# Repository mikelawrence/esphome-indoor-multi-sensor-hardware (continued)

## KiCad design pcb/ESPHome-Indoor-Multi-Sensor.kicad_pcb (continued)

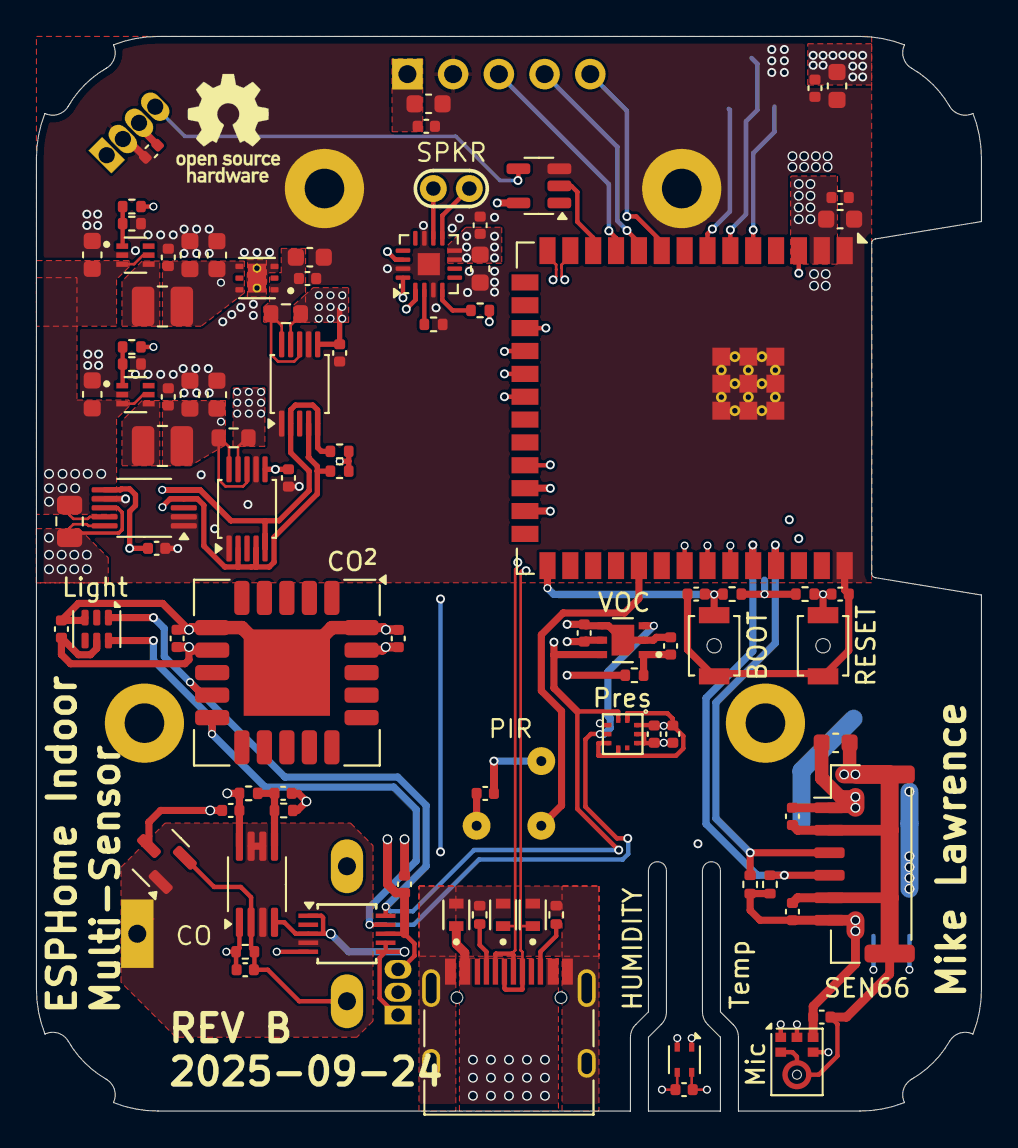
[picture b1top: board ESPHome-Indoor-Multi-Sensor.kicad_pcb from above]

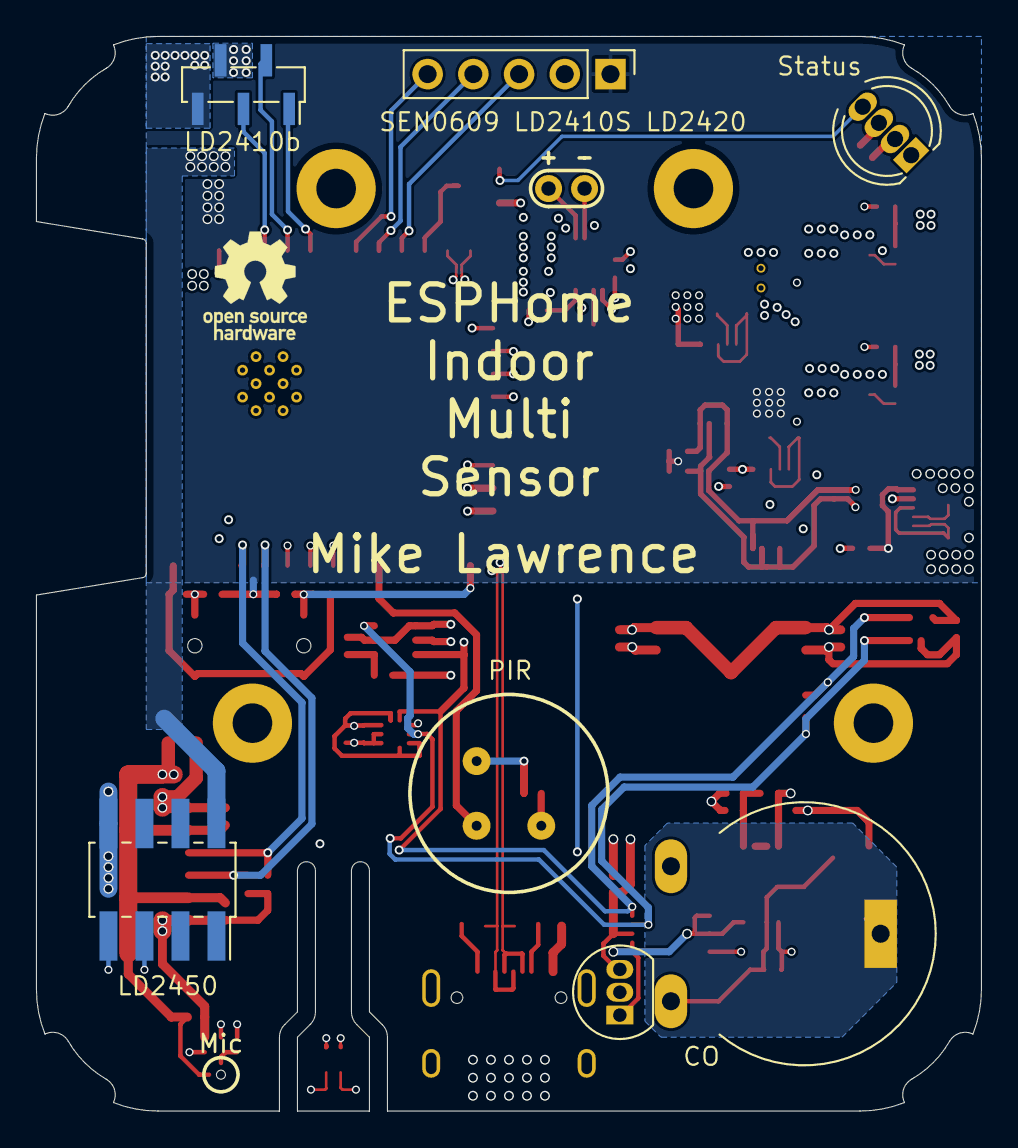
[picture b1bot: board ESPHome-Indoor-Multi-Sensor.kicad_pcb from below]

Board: 4 copper layers, 52.5 x 59.7 mm, 113 parts (9 on the bottom side), 48 nets.

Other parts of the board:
T1, T2, T3, T4, T5, T6, T7, T8, T9, T10: Tab
TEXT0, TEXT0#2: OSHW-Logo_5.7x6mm_SilkScreen

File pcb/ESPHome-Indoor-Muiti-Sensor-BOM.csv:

"Qty","Reference","Value","Description","DNP","Manufacturer","Part Number"
"11","C1,C4,C5,C22,C25,C26,C27,C31,C34,C36,C37","1uF","Capacitor, 1uF, MLCC, 25V, X5R, 10%, 0402","","Samsung","CL05A105KA5NQNC"
"12","C2,C3,C8,C9,C11,C12,C13,C15,C16,C18,C19,C30","22uF","Capacitor, 22uF, MLCC, 6.3V, X5R, 20%, 0603","","Murata","GRM188R60J226MEA0D"
"18","C6,C7,C10,C14,C17,C20,C21,C23,C24,C28,C29,C32,C33,C35,C38,C39,C40,C41","100nF","Capacitor, 100nF, MLCC, 50V, X7R, 10%, 0402","","Samsung","CL05B104KB54PNC"
"1","D4","NeoPixel_THT","RGB LED with integrated controller, 5mm/8mm LED package","","Adafruit","1938"
"3","D1,D2,D3","ESDA8P80-1U1M","TVS, Unidirectional high power, QFN-2","","STMicroelectronics","ESDA8P80-1U1M"
"1","J1","SEN66","6-Position, 1.25 mm pitch, Wire-to-Board connector","","JST","BM06B-GHS-TBT"
"1","J2","USB-C","Connector, USB 2.0, 16P, Type-C, Receptacle","","Phoenix Contact","1332645"
"1","J3","SEN0609","Generic connector, 2.54mm spacing, single row, 01x05 (TLW-105-06-T-S)","","Samtec","CES-105-01-T-S"
"1","J4","LD2410","Generic connector, 1.27mm spacing, single row, 01x05","","Samtec","RSM-105-02-S-S"
"1","J5","SPKR","Solder Holes for up to 24 ga wire","","Same Sky","CMS-251437-24SP-X8 "
"1","J6","LD2450","Socket, 8 position, 2mm spacing, dual row, 02x04, SMT","","Molex","79109-1003"
"2","L1,L2","1uH","Inductor, 1uH, 3.3A, 20%, 1008","","Murata","DFE252012F-1R0M=P2"
"1","MK1","ICS-43434","TDK InvenSense MEMS Microphone, 24-bit I2S, 65 dBA SNR, LGA-6","","TDK InvenSense","ICS-43434"
"1","Q1","MMBFJ201","20mA min, 35V, 30mOhm max, 3-10V Vgs(off), N-Channel JFET, SOT-23","","Onsemi","MMBFJ201"
"1","R1","499KΩ","Resistor, 499KΩ, 62.5mW, 1%, 0402","","Vishay / Dale","CRCW0402499KFKED"
"1","R3","634KΩ","Resistor, 634KΩ, 62.5mW, 1%, 0402","","Vishay / Dale","CRCW0402634KFKED"
"1","R4","453KΩ","Resistor, 453KΩ, 62.5mW, 1%, 0402","","Vishay / Dale","CRCW0402453KFKED"
"1","R8","68mΩ","Current Sense Resistor, 68mΩ, 400mW, 1%, 75ppm, 0603","","Vishay","WSLP0603R0680FEA"
"1","R9","150mΩ","Current Sense Resistor, 150mΩ, 250mW, 1%, 75ppm, 0805","","Vishay","WSL0805R1500FEA18"
"1","R10","80mΩ","Current Sense Resistor, 80mΩ, 400mW, 1%, 75ppm, 0603","","Vishay","WSLP0603R0800FEB"
"1","R14","4.7Ω","Resistor, 4.7Ω, 62.5mW, 1%, 0402","","Vishay / Dale","CRCW04024R70FKED"
"1","R15","64.9KΩ","Resistor, 64.9KΩ, 62.5mW, 1%, 0402","","Vishay / Dale","CRCW040264K9FKED "
"1","R21","133KΩ","Resistor, 133KΩ, 62.5mW, 1%, 0402","","Vishay / Dale","CRCW0402133KFKED"
"2","R12,R13","10KΩ","Resistor, 10KΩ, 62.5mW, 1%, 0402","","Vishay / Dale","CRCW040210K0FKED"
"4","R2,R5,R11,R16","100KΩ","Resistor, 100KΩ, 62.5mW, 1%, 0402","","Vishay / Dale","CRCW0402100KFKED"
"6","R6,R7,R17,R18,R19,R20","5.1KΩ","Resistor, 5.1KΩ, 62.5mW, 1%, 0402","DNP","Vishay / Dale","CRCW04025K10FKED"
"1","SW1","BOOT","Switch, SMD","","Omron","B3U-1000P"
"1","SW2","RESET","Switch, SMD","","Omron","B3U-1000P"
"1","U1","SN74LV1T34DBV","IC, Single Power Supply, Single Buffer GATE, CMOS Logic, Level Shifter, SOT-23-5","","Texas Instruments","SN74LV1T34DBV"
"1","U3","MAX98357A","Mono DAC with amplifier, I2S, PCM, TDM, 32-bit, 96khz, 3.2W, TQFP-16","","Maxim","MAX98357AETE"
"1","U4","TLV75533PDRV","500mA Low Dropout Voltage Regulator, Fixed Output 3.3V, WSON6","","Texas Instruments","TLV75533PDRV"
"1","U6","ESP32-S3-WROOM-2-N32R16V","RF Module, ESP32-S3 SoC, Wi-Fi 802.11b/g/n, Bluetooth, BLE, 32-bit, 3.3V, onboard antenna, SMD","","Espressif","ESP32-S3-WROOM-2-N32R16V"
"1","U7","INA228","IC, 85-V, 20-Bit, Ultra-Precise Power-Energy-Charge Monitor With I2C Interface, VSSOP-10","","Texas Instruments","INA228AIDGSR"
"1","U8","TSL2591","Light to digital converter, 2.7 to 3.6V Vdd, DFN-6","","AMS","TSL2591"
"1","U9","SGP41","Indoor Air Quality Sensor, MOx based, DFN-6","","Sensirion","SGP41-D-R4 "
"1","U10","SCD41","Photoacoustic CO2 sensor, I2C, 2.4-5.5 V, High accuracy  400 - 5000 ppm","","Sensirion","SCD41-D-R2"
"1","U11","BMP581","Barometric Pressure Sensor, 24-bit, Low-power and Low-noise, SMD","","Bosch Sensortec ","BMP581"
"1","U12","MCP6042","Dual Operational Amplifiers, Rail-to-Rail Input/Output, MSOP-8","","Microchip","MCP6042T-I/MS"
"1","U13","ADS1115","Ultra-Small, Low-Power, I2C-Compatible, 860-SPS, 16-Bit ADCs With Internal Reference, Oscillator, and Programmable Comparator, VSSOP-10","","Texas Instruments","ADS1115IDGS"
"1","U14","SHT45","Digital Humidity and Temperature Sensor, ±1%RH, ±0.1°C, I2C, 1.08-3.6V, 16bit, DFN-4","","Sensirion","SHT45-AD1B-R2"
"1","U15","EKMC1603111","Passive Infrared (PIR) Motion Sensor, THT","","Panasonic","EKMC1603111"
"1","U16","TGS5141","Carbon Monoxide Sensor, Long life, THT","","Figaro","TGS5141-P00"
"1","U17","DS18S20","High-Precision 1-Wire Digital Thermometer TO-92","","Maxim","DS18S20+"
"2","U18,U19","INA238","IC, 85V, 16-Bit, High-Precision Power Monitor With I2C Interface, VSSOP-10","","Texas Instruments","INA238AIDGSR"
"2","U2,U5","TLV62568DRL","High Efficiency Synchronous Buck Converter, Adjustable Output 0.6V-5.5V, 1A, SOT-563-6","","Texas Instruments","TLV62568DRL"

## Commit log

2025-07-08 README point to installtion and configuration site.
2025-07-09 Revert "Create .gitattributes"
    This reverts commit bf81a217180fd2e67a16f5b51bebdeff474d3883.
2025-09-23 Rev A Updates
    Support LD2410S and LD2420 Radars in same connector as C4001. Now using 3.3V instead of 5V.
    Removed Power control for Radars.
    Added DS18S20 to measure CO sensor temperature directly.
    Reworked SHT4X layout to reduce thermal transfer.
2025-09-23 Rev B Updates
    Fix image link error for enclosure
2025-09-23 Fix one more bad image link
2025-09-23 Cleanup schematic, BOM and update gerber files
2025-09-23 Minor cleanup
2025-09-23 Add new ina228 to other power supplies
    Not finished
2025-09-24 Rev B Updates finish adding power monitors for 3.3V and 3.3VA
    Removed speaker gain jumper
2025-09-24 Add Rev B notes to schematic
    Update BOM
2025-09-24 Rev B updates
2025-09-24 Minor edits
2025-09-29 BOM Updates
    No PCB changes. This is still Rev.B
2025-10-01 Update Enclosure Files to latest
    Add Angle Wallplate
2025-10-01 Resize images
2025-10-01 Center images
2025-10-01 Rename Wallplate files
2025-10-01 Fix paths
2025-10-01 Fix more paths
2025-10-03 Add Stencil Jig step files and fusion project
2025-10-03 Update 3D Printing files
2025-10-04 Adjustments to Jig
    Works better with PLA and 2mm stainless steel pins.
    Add hole under PCB to make it easier to remove the PCB.
2025-10-04 Fix missing USB-C cutout in front body
2025-10-04 Update README.md
    Fix path pointing to wrong repository
2025-10-05 Design now uses one ina228 and two ina232 power sensors
    Reduces cost without sacrificing functionality. Mainly wanted power supply voltage and currents.
